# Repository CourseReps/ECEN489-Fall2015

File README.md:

# Data Acquisition &amp; Embedded Systems

## Description

The goal of this multidisciplinary project-based laboratory course is to provide instruction on data acquisition, system-level integration and design through a range of hands-on activities that complement the traditional classroom experience.
This includes circuit prototyping, PCB fabrication, microcontrollers and C++ programming, networking, and data visualization.
The main focus is on modular application development, algorithms, information management, control and actuation.
In addition, emphasis is put on team work, presentation skills, time management, creativity and innovation.

## Objectives

1. Enhance engineering education by facilitating learning through engineering projects.
2. Review the basics of circuit building, programming concepts, computer-aided design tools, the fundamentals of microcontrollers.
3. Foster leadership and team work, with division of labor, complementary tasks, discussion and integration.
4. Develop the ability to bridge theoretical concepts and practical tasks.
5. Master elements of experiential learning such as abstract conceptualization, active experimentation, concrete experience, reflective observation.
6. Improve transferable engineering skills and the ability to integrate different concepts.
7. Develop confidence and leadership.
8. Promote creativity and critical thinking.
9. Refine presentation skills and the ability to conduct and manage projects.

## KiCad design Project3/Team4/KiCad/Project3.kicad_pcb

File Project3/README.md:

# Project 3

# Team Assignment

## [Team 1](https://github.com/CourseReps/ECEN489-Fall2015/wiki/project3-team1)

* Kartic Bhargav
* Thomas Branyon
* Henry Xiangdong Yu
* Kan Zheng

## [Team 2](https://github.com/CourseReps/ECEN489-Fall2015/wiki/project3-team2)

* Anthony Ramirez
* Keaton Brown
* Travis Taghavi
* Austin Taghavi
* Blade Roybal (Free Agent)

## [Team 3](https://github.com/CourseReps/ECEN489-Fall2015/wiki/project3-team3)

* Kaimen Walters
* Steven Jinpeng You
* Hai Li
* Pranay Eedara

## [Team 4](https://github.com/CourseReps/ECEN489-Fall2015/wiki/project3-team4)

* Udaya Bhaskar Kothapalli
* Abhay Anand
* Cooper Rehn
* Seungwon Yoon

# Simulation/Model Testing
In order to verify our models and algorithms, all the teams will test their models using the same values/input files.
##Problem 1
For the single-bucket volume estimation problem, we define the model to have the following parameters (equivalent to a standart 500ml beaker):
* Bucket diameter - 8cm
* Bucket height - 12cm
* Hole/leak diameter - 5mm
* Max flowrate - 3.5 L/min
    - Flowrate is assumed to be linear with PWM value between 0 and 255. i.e., PWM of 255 will yield a flowrate of 3.5L/min, and a PWM of 0 will yield a flow of 0L/min

Our input to the simulation will just be these four values, plus two more - a setpoint, and a height "jump" that occurs when the object is dropped in. To start, we will use the following test cases:
* Setpoint = 6cm, jump = 1cm
* Setpoint = 3cm, jump = 2cm

The input file will be all 6 values comma-separated. Example:

File 1:

    8, 12, 5, 3.5, 6, 1
    
File 2:

    8, 12, 5, 3.5, 3, 2

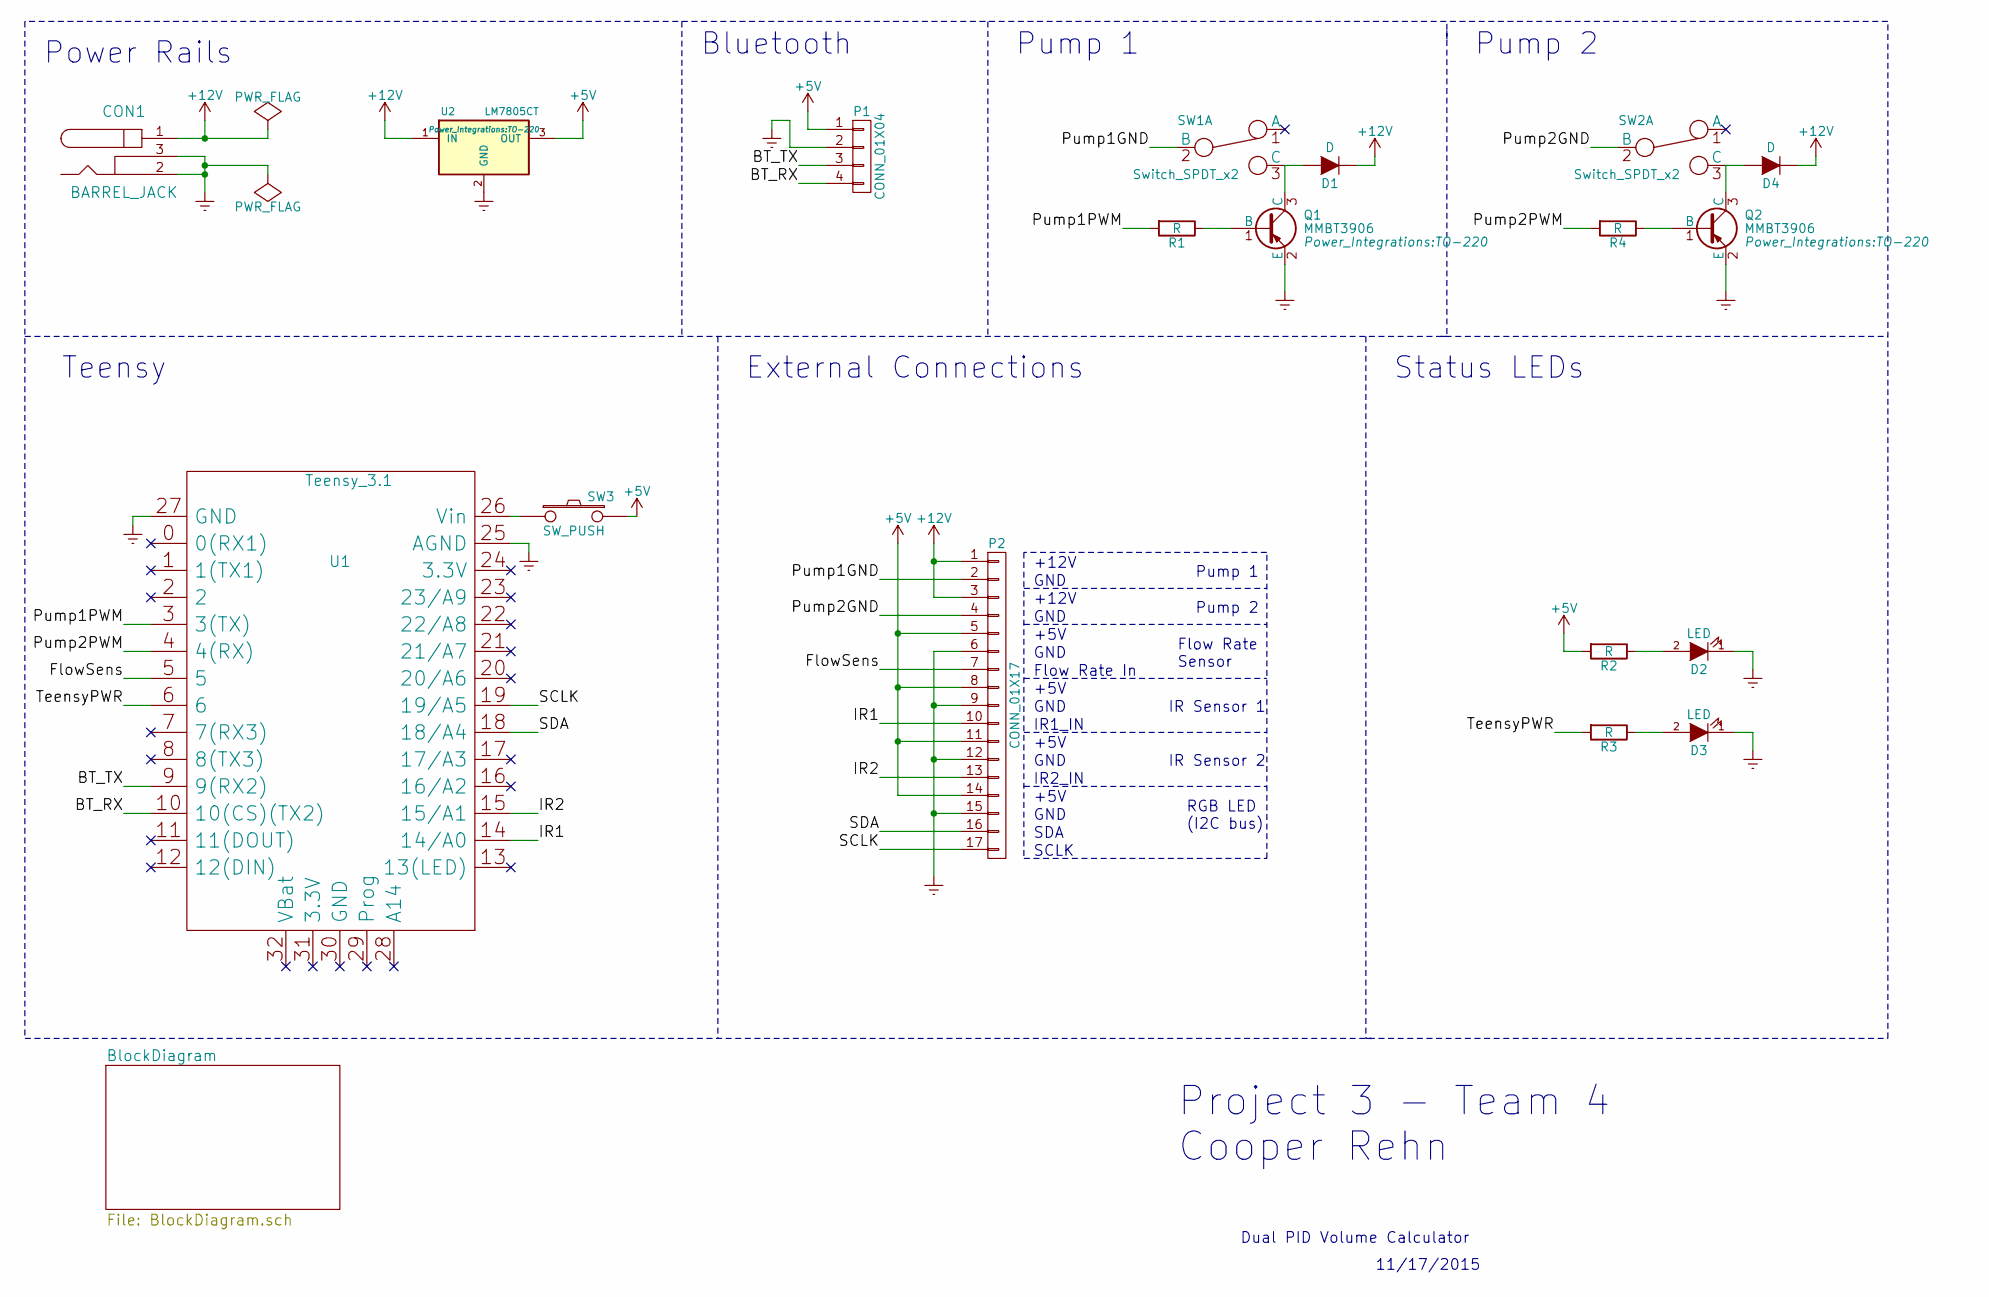
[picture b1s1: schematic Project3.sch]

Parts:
CON1: BARREL_JACK
D1, D4: D; Diode_DO-41_SOD81_Horizontal_RM10
D2, D3: LED; LED-3MM
P1: CONN_01X04; Pin_Header_Straight_1x04
P2: CONN_01X17; mors_17p
Q1, Q2: MMBT3906; TO-220
R1, R2, R3, R4: R; Resistor_Horizontal_RM10mm
SW1, SW2: Switch_SPDT_x2; SPDT-ThroughHole
SW3: SW_PUSH; SW_PUSH_SMALL
U1: Teensy_3.1; Teensy-3.1
U2: LM7805CT; TO-220

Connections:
+5V: P1.1, P2.5, P2.8, P2.11, P2.14, R2.2, SW3.2, U2.3 (OUT)
+12V: CON1.1, D1.1 (K), D4.1 (K), P2.1, P2.3, U2.1 (IN)
/BT_RX: P1.4, U1.10 (10(CS)(TX2))
/BT_TX: P1.3, U1.9 (9(RX2))
/FlowSens: P2.7, U1.5
/IR1: P2.10, U1.14 (14/A0)
/IR2: P2.13, U1.15 (15/A1)
/Pump1GND: P2.2, SW1.2 (B)
/Pump1PWM: R1.2, U1.3 (3(TX))
/Pump2GND: P2.4, SW2.2 (B)
/Pump2PWM: R4.2, U1.4 (4(RX))
/SCLK: P2.17, U1.19 (19/A5)
/SDA: P2.16, U1.18 (18/A4)
/TeensyPWR: R3.2, U1.6
Earth: CON1.2, CON1.3, D2.1 (K), D3.1 (K), P1.2, P2.6, P2.9, P2.12, P2.15, Q1.2 (E), Q2.2 (E), U1.25 (AGND), U1.27 (GND), U2.2 (GND)
unnamed: D1.2 (A), Q1.3 (C), SW1.3 (C)
unnamed: D2.2 (A), R2.1
unnamed: D3.2 (A), R3.1
unnamed: D4.2 (A), Q2.3 (C), SW2.3 (C)
unnamed: Q1.1 (B), R1.1
unnamed: Q2.1 (B), R4.1
unnamed: SW3.1, U1.26 (Vin)

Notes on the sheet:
+12V
GND
+5V
Flow Rate In
IR1_IN
IR2_IN
SDA
SCLK
Pump 1
Pump 2
Flow Rate Sensor
IR Sensor 1
IR Sensor 2
RGB LED (I2C bus)
Power Rails
Bluetooth
Teensy
External Connections
Status LEDs
Project 3 - Team 4 Cooper Rehn
Dual PID Volume Calculator
11/17/2015

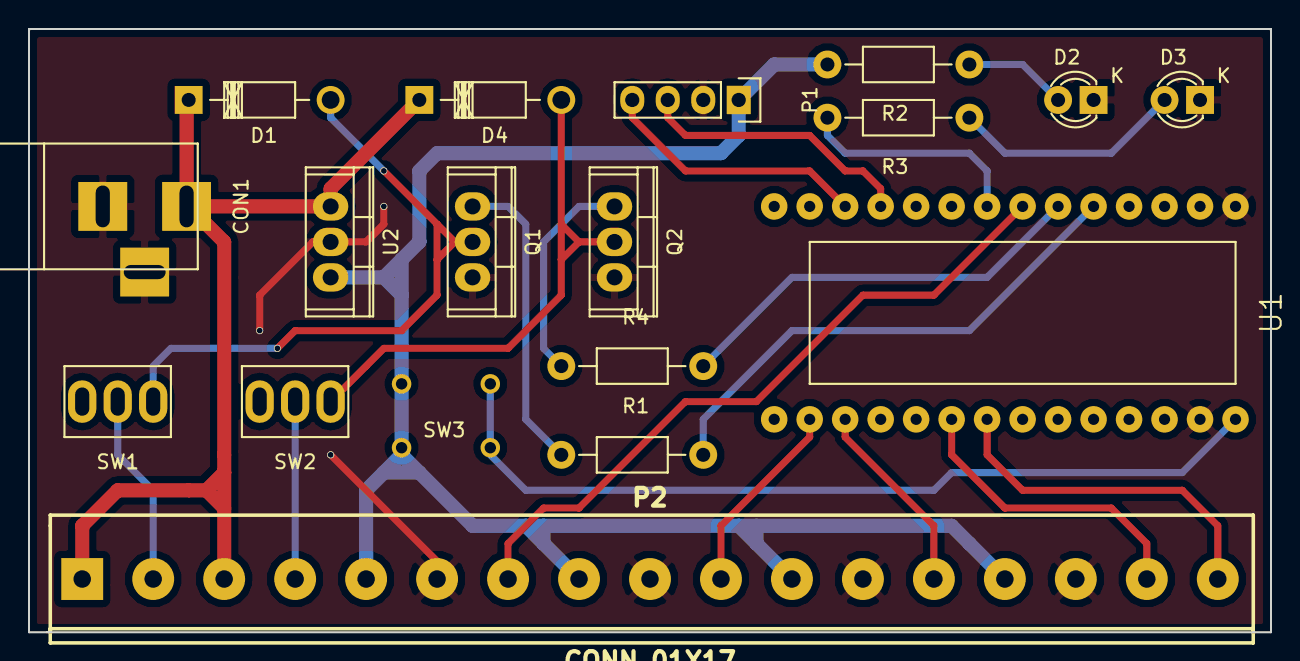
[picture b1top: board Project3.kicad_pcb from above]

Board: 2 copper layers, 88.9 x 43.2 mm, 18 parts (0 on the bottom side), 22 nets.

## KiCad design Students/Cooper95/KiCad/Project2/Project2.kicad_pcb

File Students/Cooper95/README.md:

# Identity

* Name: Cooper Rehn
* GitHub ID: Cooper95
* NetID : Cooper95

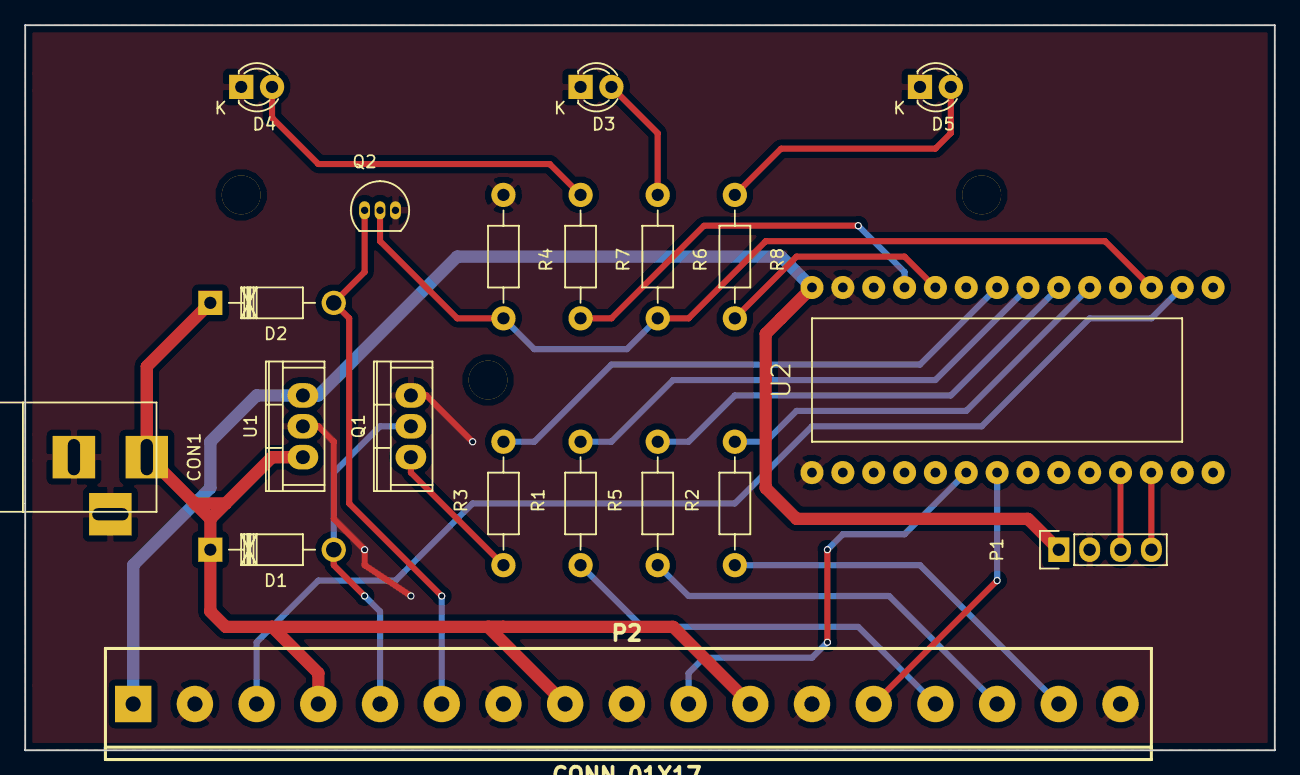
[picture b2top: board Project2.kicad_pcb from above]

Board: 2 copper layers, 102.9 x 59.7 mm, 20 parts (0 on the bottom side), 24 nets.

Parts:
CON1: BARREL_JACK
D1, D2: D; Diode_DO-41_SOD81_Horizontal_RM10
D3, D4, D5: LED; LED-3MM
P1: CONN_01X04; Pin_Header_Straight_1x04
P2: CONN_01X17; mors_17p
Q1: MMBT3906; TO-220
Q2: BS170; TO-92_Inline_Narrow_Oval
R1, R2, R3, R4, R5, R6, R7, R8: R; Resistor_Horizontal_RM10mm
U1: LM7805CT; TO-220
U2: Teensy_3.1; Teensy-3.1

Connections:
+5V: P1.1, P2.1, U1.3, U2.26
+12V: CON1.1, D1.1, D2.1, P2.4, P2.8, P2.11, U1.1
/BT_RX: P1.4, U2.10
/BT_TX: P1.3, U2.9
/FS1: P2.10, U2.4
/FS2: P2.13, U2.5
/IR_In: P2.3, U2.14
/LED_B: R2.2, U2.17
/LED_G: R5.2, U2.18
/LED_R: R1.2, U2.19
/LowLevelLED: R8.2, U2.22
/PWR_LED: R7.2, U2.23
/PumpGND: D1.2, P2.5, Q1.3
/PumpPWM: R3.2, U2.20
/SolenoidCtrl: Q2.2, R4.2, R6.2, U2.15
/SolenoidOut: D2.2, P2.6, Q2.1
GND: CON1.2, CON1.3, D3.1, D4.1, D5.1, P1.2, P2.2, P2.7, P2.9, P2.12, P2.17, Q1.2, Q2.3, R4.1, U1.2, U2.25, U2.27
unnamed: D3.2, R6.1
unnamed: D4.2, R7.1
unnamed: D5.2, R8.1
unnamed: P2.14, R1.1
unnamed: P2.15, R5.1
unnamed: P2.16, R2.1
unnamed: Q1.1, R3.1

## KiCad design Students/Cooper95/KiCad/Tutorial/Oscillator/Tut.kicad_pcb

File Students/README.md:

# Enrolled Students and Faculty Members

## Undergraduate Students

* Thomas Branyon, aggiebass2015, [tbranyon](https://tbranyon.github.io/)
* Keaton Brown, keabro, [Keabro](https://Keabro.github.io/)
* Anthony Ramirez, agramir16, [agramir16](https://agramir16.github.io/)
* Blade Roybal, bladero, [bladeroybal](http://bladeroybal.github.io/)
* Cooper Rehn, cooper95, [Cooper95](https://Cooper95.github.io/)
* Kaimen Walters, kaimen.walters, [kaimen-walters](https://kaimen-walters.github.io/)
* Seungwon Yoon, ysw0927, [buttonsense](https://buttonsense.github.io/yoon)
* Jinpeng You, stevenyou92, [stevenyou92](https://stevenyou92.github.io/)
* Xiangdong Yu, henryyu8, [henryyu8](http://henryyu8.github.io./)

## Graduate Students

* Abhay Anand, abhaysanand, [abhaysanand](https://abhaysanand.github.io/)
* Pranay Eedara, epranaykumar, [epranaykumar](https://epranaykumar.github.io/)
* Kartic Bhargav, karticbhargav170, [karticbhargav](https://karticbhargav.github.io/)
* Udaya Bhaskar Kothapalli, udaybhaskar.k, [ubkothapalli](http://ubkothapalli.github.io/)
* Hai Li, lh1234, [lihai1991](https://lihai1991.github.io/)
* Austin Taghavi, ataghavi, [ATaghavi](https://ATaghavi.github.io/)
* Travis Taghavi, travistag, [travistag](https://travistag.github.io/)
* Kan Zheng, wszk1992, [wszk1992](http://wszk1992.github.io/Kan-Zheng)

## Faculty Members

* Jean-Francois Chamberland, chmbrlnd, [chmbrlnd](https://chmbrlnd.github.io/)
* Gregory H. Huff, ghuff, [ghuff](https://github.com/ghuff)

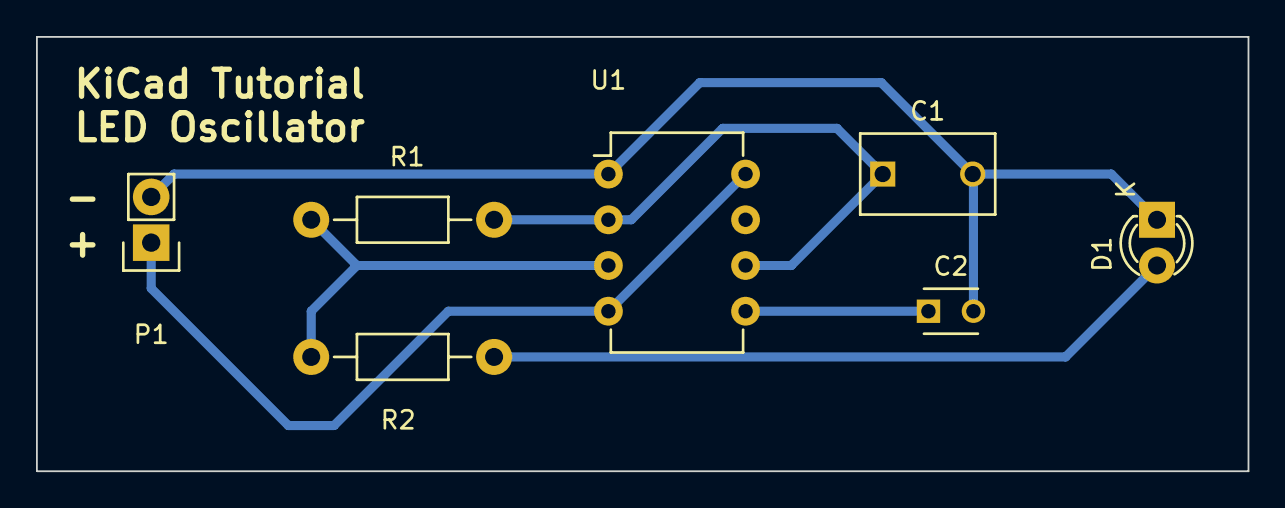
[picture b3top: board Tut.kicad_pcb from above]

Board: 2 copper layers, 67.3 x 24.1 mm, 7 parts (0 on the bottom side), 6 nets.

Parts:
C1: 100uF; C_Disc_D7.5_P5
C2: .01uF; C_Disc_D3_P2.5
D1: LED; LED-3MM
P1: CONN_01X02; Pin_Header_Straight_1x02
R1: 10k; Resistor_Horizontal_RM10mm
R2: 470; Resistor_Horizontal_RM10mm
U1: LM555N; DIP-8_W7.62mm

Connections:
GND: C1.2, C2.2, D1.1, P1.2, U1.1
unnamed: C1.1, R1.2, U1.2, U1.6
unnamed: C2.1, U1.5
unnamed: D1.2, R2.1
unnamed: R1.1, R2.2, U1.3
VCC: P1.1, U1.4, U1.8

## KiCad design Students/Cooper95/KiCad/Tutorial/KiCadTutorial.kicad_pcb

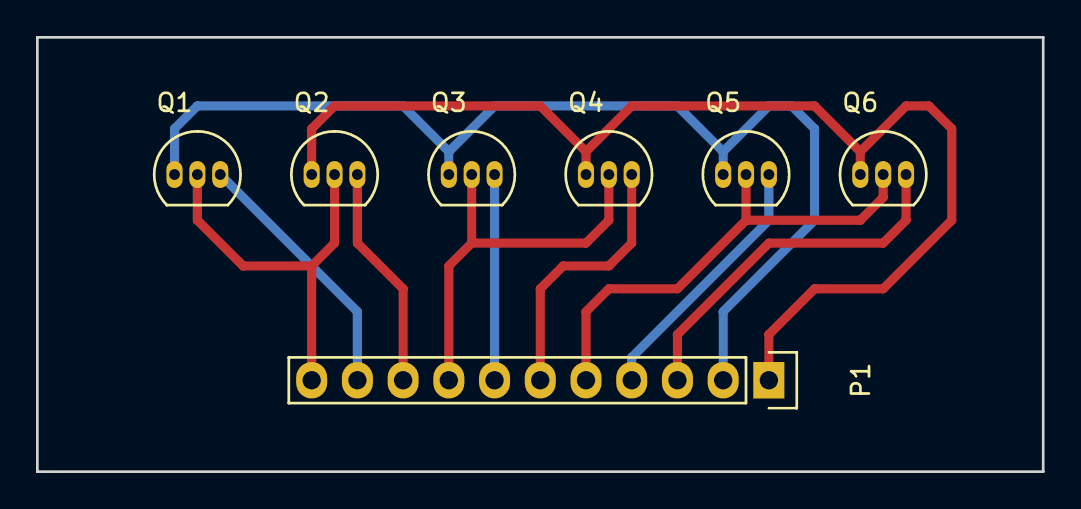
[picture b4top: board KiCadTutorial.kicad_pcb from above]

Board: 2 copper layers, 55.9 x 24.1 mm, 7 parts (0 on the bottom side), 11 nets.

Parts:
P1: CONN_01X11; Pin_Header_Straight_1x11
Q1, Q2, Q3, Q4, Q5, Q6: BS170; TO-92_Inline_Narrow_Oval

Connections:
unnamed: P1.1, Q2.1, Q4.1, Q6.1
unnamed: P1.2, Q1.1, Q3.1, Q5.1
unnamed: P1.3, Q6.3
unnamed: P1.4, Q5.3
unnamed: P1.5, Q5.2, Q6.2
unnamed: P1.6, Q4.3
unnamed: P1.7, Q3.3
unnamed: P1.8, Q3.2, Q4.2
unnamed: P1.9, Q2.3
unnamed: P1.10, Q1.3
unnamed: P1.11, Q1.2, Q2.2

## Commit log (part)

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2015-09-16 minor change
2015-09-16 Adding files for KiCad tutorial
2015-09-16 Adding Assignment 2 Programming Challenge
2015-09-16 Add optout3
2015-09-16 adding optout 3
2015-09-16 Adding Assignment 3
    Broken
2015-09-16 chaning port for server
2015-09-16 Updating Assignment 3
    Working now
2015-09-16 Added option to choose port in client
2015-09-16 Minor change to 3optout client
2015-09-16 Fixed format to ensure jpg rather than png
2015-09-16 Minor change in client
2015-09-16 cmake assignment3
2015-09-16 Deleting vestigial files.
2015-09-16 Assignment 4.
2015-09-17 Adding KiCad tutorial files
2015-09-17 Updating pictures
2015-09-17 3optout
2015-09-17 change name
2015-09-17 added tutorial folder :
2015-09-17 Updating 1optout
2015-09-18 Deleting .gitignore
2015-09-18 Adding 3optout
2015-09-18 Rename README to README.md
2015-09-18 Assignment 4
2015-09-18 cleanup
2015-09-18 optout3
2015-09-18 optout3 library files
2015-09-18 Rename arduinocode to arduinocode.ino
2015-09-18 optout3 readme files
2015-09-18 example of sqilte in c
2015-09-18 add the cmakelist
2015-09-20 assignment4
2015-09-20 4optout
2015-09-21 Adding server and client files
2015-09-21 Changing directory and adding CMakeLists
2015-09-21 Editing server so that it doesn't leave db open
2015-09-21 minor update
2015-09-21 Updating README.md
2015-09-21 final
2015-09-21 small deletions
2015-09-21 deleting unwanted files
2015-09-21 optout4 broadcast and server files
2015-09-21 Adding optout 4
2015-09-21 Adding port number as command line arg
2015-09-21 add optout4
2015-09-21 remove idea files
2015-09-21 Adding Assignment 4
2015-09-21 Assignment 5.
2015-09-22 Assignment 5
2015-09-23 update assignments
2015-09-23 Updating server.cpp
2015-09-24 assignment5
2015-09-24 add 4optout
2015-09-24 aaaa
2015-09-24 delete
2015-09-25 assn2 update
2015-09-25 optout4 updates
2015-09-25 Sample codes for Bluetooth tutorial
2015-09-25 Added assignment 5
2015-09-25 Adding Assignment 5 files
2015-09-25 no message
2015-09-25 Adding Assignment 5
2015-09-25 Updating Assignment 5
2015-09-25 asdf
2015-09-25 adding quickfire
2015-09-29 Adding readme
2015-09-29 Edited client.cpp
2015-09-29 assignment6
2015-09-30 Assignment 6
2015-09-30 initial commit of 6optout
2015-09-30 6optout
2015-09-30 Adding 6optout
2015-09-30 Editing README.md
2015-09-30 Adding 6optout files
2015-09-30 Add readme for 6optout
2015-09-30 added assignment 6
2015-09-30 Fixed Server.cpp bug
2015-09-30 optout6 files
2015-09-30 Changed to non-privileged port on client
2015-09-30 add optOut6
2015-09-30 Updated README for 6optout
2015-09-30 optout6 modification
2015-09-30 Adding Assignment 6
2015-09-30 update tutorials
2015-09-30 Assignment6 revision
2015-09-30 removing junk
2015-09-30 optout6 code update
2015-10-02 Corrected 6optout sources
2015-10-03 modify 6optout
2015-10-05 Fixed quickfire 3 files
2015-10-05 Adding Optout4
2015-10-05 test2foroptout7
2015-10-05 Adding quickfire and 7optout
2015-10-05 commiting 6optout and quickfire
2015-10-05 7optout
2015-10-05 Adding teams for Project 1.
2015-10-05 Adding graders.
2015-10-06 add 7optout
2015-10-06 Various updated files - merging
2015-10-06 Initial commit of 7optout - unstable
2015-10-06 Updated 7optout files
2015-10-07 Adding optout6
2015-10-07 optout6 edit teensy code
2015-10-07 optout7
2015-10-07 quickfire
2015-10-07 making a tiny change to ui
2015-10-07 Graders.
2015-10-07 Updating list of students in graders.cpp.
2015-10-07 optout7 threading
2015-10-08 optout7 threading update
2015-10-08 adding motor control tutorial sketch
2015-10-08 modified 7optout
2015-10-09 Adding client for Project1
2015-10-11 modify 7optout
2015-10-11 Adding PWM and Sensor Measurement
2015-10-12 small changes
2015-10-12 Updating client
2015-10-12 1project bluetoothbasic
2015-10-13 qtplot
2015-10-13 1project bluetooth server
2015-10-14 Adding Project1 Files
2015-10-14 Adding 7optout
2015-10-14 Adding project 1 sketch
2015-10-14 Project 1 code
2015-10-14 Adding arduino sensor reading code
2015-10-14 add project1
2015-10-14 plots for 1project
2015-10-14 Updating Proj 1
2015-10-15 Added new visualisation QT Creator project
2015-10-16 adding teensy code
2015-10-16 Adding Project1Server
2015-10-16 Final project 1 teensy sketch
2015-10-16 adding server
2015-10-16 updating server
2015-10-16 Project1 NUC code
2015-10-16 update server
2015-10-16 updating
2015-10-16 adding server and client and updating vis
2015-10-16 Updating Project1Server
2015-10-16 Updating visuals
2015-10-16 updating arduino code
2015-10-16 1project BTclient server working
2015-10-19 Adding teams for project 2.
2015-10-21 Add Schematic Project1
2015-10-21 Add CustomComponents
2015-10-23 adding arduino files for PID
2015-10-23 updating files
2015-10-23 adding proj2 temp sketch
2015-10-25 add project1 programs
2015-10-25 rm team2 directory in project1
2015-10-26 adding arduino PID code
2015-10-26 Adding Project2 folder
2015-10-28 Arduino code updated
2015-10-30 PID working code
2015-11-02 Adding proj 2 screenshots
2015-11-03 Adding teensy bluetooth prj2
2015-11-03 updating project 2 teensy sketch for BT
2015-11-04 2project Qt console
2015-11-04 2project Teensy code
2015-11-04 2project modified Qt
2015-11-04 2project teensy code updated
2015-11-04 Create project2
2015-11-04 updating plotter
2015-11-04 Adding server for P2
2015-11-04 modifying server
2015-11-04 updated arduino code
2015-11-04 project 2 files
2015-11-04 add images
2015-11-04 updated teensy sketch
2015-11-04 adding some debugging to server
2015-11-04 adding QT and Arduno
2015-11-06 Final Project 2
2015-11-06 deleting garbage
2015-11-06 adding board image
2015-11-06 updating server for bt reading
2015-11-06 add image
2015-11-09 solidworks
2015-11-09 Add Screenshots
2015-11-09 adding qt image
2015-11-13 File Clean up
2015-11-13 Project 3 schem
2015-11-13 pcb for project2
2015-11-13 Adding BOM
    v1
2015-11-13 Project 3 PCB
2015-11-15 Finished project 3 board and BOM
2015-11-16 Adding project 3 PCB files
2015-11-16 Add PCB Screenshot
2015-11-16 Moving project 3 PCB files to Team 4 folder
2015-11-16 Adding prelimiary Python code for the model
2015-11-16 add libraries used
2015-11-16 clean up folder
2015-11-16 Add PCB Screenshots
2015-11-16 arduino code for team4
2015-11-17 updates in 2project
2015-11-17 3project Qt model
2015-11-17 simulator demo
2015-11-18 modify simulator
2015-11-18 Adding Project3 Wiki images
2015-11-18 part1upload
2015-11-18 Update images in Project3
2015-11-18 update: adding label
2015-11-18 Adding PCB screens and block diagram
2015-11-18 3project image1
2015-11-18 singlt tank image
2015-11-18 remove image
2015-11-18 Adding project3 files
2015-11-18 Adding model stuff
2015-11-18 single tank image modified
2015-11-18 Adding images
2015-11-18 coupled tank image
2015-11-20 Adding images for project 3 wiki
2015-11-20 Adding Flow Rate calibration
    Measures flow rate from hall sensor and time taken to calibrate using a
    1L bottle. Updated constant can be used improve accuracy
2015-11-23 Update flowRate
    Updated to prevent max pump output at beginning
2015-11-23 Update flowRate
    Try 3
2015-11-30 modified for object volume calc
2015-11-30 Full model without visualization
2015-11-30 adding database
2015-11-30 update simulator
2015-11-30 committing database changes intermittantly, so that real time plotting is possible
2015-12-02 Project3 Server BT comms
2015-12-02 Adding ARduino code
2015-12-04 Updating proj 3 files
2015-12-04 updated project 3
2015-12-04 Adding teensy code (unstable). Base is Abhay Anand - Project 2.
2015-12-04 Adding pump cablibration routine
2015-12-06 Adding pictures for documentation
2015-12-06 fixing images
2015-12-06 add project 3
2015-12-07 modify project3
2015-12-07 Adding project 3 calibrations
2015-12-07 Adding newest teensy code. Object detection for tank 1 and comms for both tanks working. Volume calculation is off by a factor of 5-10.
2015-12-07 Adding PId code
2015-12-07 Adding PID2 code
2015-12-08 adding screenshot
2015-12-08 Committing working Project3-part1 code for Teensy
2015-12-08 proj3
2015-12-08 added photo
2015-12-09 proj3 pics
2015-12-09 Adding Project3 images
2015-12-09 adding calibration curves
2015-12-09 adding pix
2015-12-09 final modification for QT
2015-12-09 project3 team4 QT
2015-12-11 reorganizing project3 files and folders
2015-12-11 reorganizing proj3 of team4 files and folders
